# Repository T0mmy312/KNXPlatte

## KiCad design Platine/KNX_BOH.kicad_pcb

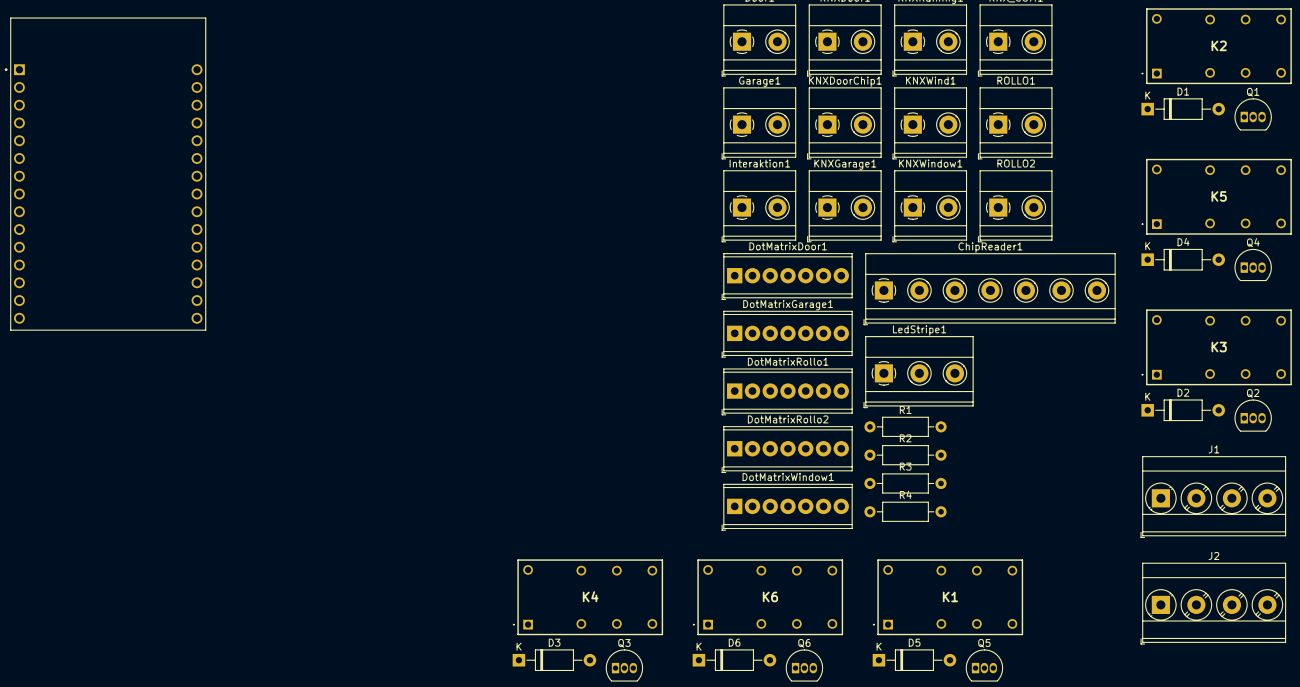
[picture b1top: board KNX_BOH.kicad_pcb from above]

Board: 2 copper layers, 44 parts (0 on the bottom side), 49 nets, no tracks yet.

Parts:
ChipReader1: Screw_Terminal_01x07; TerminalBlock_Phoenix_MKDS-1,5-7-5.08_1x07_P5.08mm_Horizont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
D1, D2, D3, D4, D5, D6: D; D_A-405_P10.16mm_Horizontal
Door1: Screw_Terminal_01x02; TerminalBlock_Phoenix_MKDS-1,5-2-5.08_1x02_P5.08mm_Horizont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
DotMatrixDoor1: Screw_Terminal_01x05; TerminalBlock_Phoenix_MPT-0,5-7-2.54_1x07_P2.54mm_Horizontal
DotMatrixGarage1: Screw_Terminal_01x05; TerminalBlock_Phoenix_MPT-0,5-7-2.54_1x07_P2.54mm_Horizontal
DotMatrixRollo1, DotMatrixRollo2: Screw_Terminal_01x05; TerminalBlock_Phoenix_MPT-0,5-7-2.54_1x07_P2.54mm_Horizontal
DotMatrixWindow1: Screw_Terminal_01x05; TerminalBlock_Phoenix_MPT-0,5-7-2.54_1x07_P2.54mm_Horizontal
ESP32_WROOM_32D_USB-C2: ESP32_WROOM_32D_USB-C
Garage1: Screw_Terminal_01x02; TerminalBlock_Phoenix_MKDS-1,5-2-5.08_1x02_P5.08mm_Horizont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
Interaktion1: Screw_Terminal_01x02; TerminalBlock_Phoenix_MKDS-1,5-2-5.08_1x02_P5.08mm_Horizont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
J1, J2: Conn_01x04_Pin; TerminalBlock_Phoenix_MKDS-3-4-5.08_1x04_P5.08mm_Horizontal
K1, K2, K3, K4, K5, K6: DSBT2-S-DC24V; DSBT2SDC24V
KNXDoor1: Screw_Terminal_01x02; TerminalBlock_Phoenix_MKDS-1,5-2-5.08_1x02_P5.08mm_Horizont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
KNXDoorChip1: Screw_Terminal_01x02; TerminalBlock_Phoenix_MKDS-1,5-2-5.08_1x02_P5.08mm_Horizont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
KNXGarage1: Screw_Terminal_01x02; TerminalBlock_Phoenix_MKDS-1,5-2-5.08_1x02_P5.08mm_Horizont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
KNXRaining1: Screw_Terminal_01x02; TerminalBlock_Phoenix_MKDS-1,5-2-5.08_1x02_P5.08mm_Horizont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
KNXWind1: Screw_Terminal_01x02; TerminalBlock_Phoenix_MKDS-1,5-2-5.08_1x02_P5.08mm_Horizont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
KNXWindow1: Screw_Terminal_01x02; TerminalBlock_Phoenix_MKDS-1,5-2-5.08_1x02_P5.08mm_Horizont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
KNX_COM1: Screw_Terminal_01x02; TerminalBlock_Phoenix_MKDS-1,5-2-5.08_1x02_P5.08mm_Horizont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
LedStripe1: Screw_Terminal_01x03; TerminalBlock_Phoenix_MKDS-1,5-3-5.08_1x03_P5.08mm_Horizont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
Q1, Q2, Q3, Q4, Q5, Q6: BC547; TO-92_Inline
R1, R2, R3, R4: 10k; R_Axial_DIN0207_L6.3mm_D2.5mm_P10.16mm_Horizontal
ROLLO1, ROLLO2: Screw_Terminal_01x02; TerminalBlock_Phoenix_MKDS-1,5-2-5.08_1x02_P5.08mm_Horizont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

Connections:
+3V3: DotMatrixDoor1.1, DotMatrixGarage1.1, DotMatrixRollo1.1, DotMatrixRollo2.1, DotMatrixWindow1.1, ESP32_WROOM_32D_USB-C2.1 (3V3), R1.1, R2.1, R3.1, R4.1
+5V: ChipReader1.1, ESP32_WROOM_32D_USB-C2.16 (VIN), LedStripe1.1, Q1.1 (C), Q2.1 (C), Q3.1 (C), Q4.1 (C), Q5.1 (C), Q6.1 (C)
/Relais1/Relais_COM: K1.4 (COM_1), K1.13 (COM_2), KNXRaining1.2
/Relais1/Relais_OUT: K1.8 (N.O._1), K1.9 (N.O._2), KNXRaining1.1
/Relais2/Relais_COM: K2.4 (COM_1), K2.13 (COM_2), KNXWind1.2
/Relais2/Relais_OUT: K2.8 (N.O._1), K2.9 (N.O._2), KNXWind1.1
/Relais3/Relais_COM: K3.4 (COM_1), K3.13 (COM_2), KNXDoor1.2
/Relais3/Relais_OUT: K3.8 (N.O._1), K3.9 (N.O._2), KNXDoor1.1
/Relais4/Relais_COM: K4.4 (COM_1), K4.13 (COM_2), KNXDoorChip1.2
/Relais4/Relais_OUT: K4.8 (N.O._1), K4.9 (N.O._2), KNXDoorChip1.1
/Relais5/Relais_COM: K5.4 (COM_1), K5.13 (COM_2), KNXGarage1.2
/Relais5/Relais_OUT: K5.8 (N.O._1), K5.9 (N.O._2), KNXGarage1.1
/Relais6/Relais_COM: K6.4 (COM_1), K6.13 (COM_2), KNXWindow1.2
/Relais6/Relais_OUT: K6.8 (N.O._1), K6.9 (N.O._2), KNXWindow1.1
CS_ChipReader: ChipReader1.7, ESP32_WROOM_32D_USB-C2.26 (D35)
CS_DotMatrixDoor: DotMatrixDoor1.4, ESP32_WROOM_32D_USB-C2.14 (D22)
CS_DotMatrixGarage: DotMatrixGarage1.4, ESP32_WROOM_32D_USB-C2.25 (D32)
CS_DotMatrixRollo1: DotMatrixRollo1.4, ESP32_WROOM_32D_USB-C2.24 (D33)
CS_DotMatrixRollo2: DotMatrixRollo2.4, ESP32_WROOM_32D_USB-C2.23 (D25)
CS_DotMatrixWindow: DotMatrixWindow1.4, ESP32_WROOM_32D_USB-C2.22 (D26)
GND: ChipReader1.3, D1.2 (A), D2.2 (A), D3.2 (A), D4.2 (A), D5.2 (A), D6.2 (A), DotMatrixDoor1.2, DotMatrixGarage1.2, DotMatrixRollo1.2, DotMatrixRollo2.2, DotMatrixWindow1.2, ESP32_WROOM_32D_USB-C2.2 (GND), ESP32_WROOM_32D_USB-C2.17 (GND), J1.4, J2.4, K1.16 (COIL-), K2.16 (COIL-), K3.16 (COIL-), K4.16 (COIL-), K5.16 (COIL-), K6.16 (COIL-), KNX_COM1.1, KNX_COM1.2, LedStripe1.3
KNX_Cooling: ESP32_WROOM_32D_USB-C2.28 (VN), Interaktion1.2
KNX_Garage_UP: ESP32_WROOM_32D_USB-C2.8 (D5), Garage1.1
KNX_Heating: ESP32_WROOM_32D_USB-C2.29 (VP), Interaktion1.1
KNX_ROLLO_1_DOWN: ESP32_WROOM_32D_USB-C2.19 (D12), ROLLO1.2
KNX_ROLLO_1_UP: ESP32_WROOM_32D_USB-C2.18 (D13), ROLLO1.1
KNX_ROLLO_2_DOWN: ESP32_WROOM_32D_USB-C2.21 (D27), ROLLO2.2
KNX_ROLLO_2_UP: ESP32_WROOM_32D_USB-C2.20 (D14), ROLLO2.1
KNX_Tür: Door1.1, ESP32_WROOM_32D_USB-C2.11 (D21)
MISO: ChipReader1.4, ESP32_WROOM_32D_USB-C2.10 (D19)
MOSI: ChipReader1.5, DotMatrixDoor1.3, DotMatrixGarage1.3, DotMatrixRollo1.3, DotMatrixRollo2.3, DotMatrixWindow1.3, ESP32_WROOM_32D_USB-C2.15 (D23)
unnamed: D1.1 (K), K2.1 (COIL+), Q1.3 (E)
unnamed: D2.1 (K), K3.1 (COIL+), Q2.3 (E)
unnamed: D3.1 (K), K4.1 (COIL+), Q3.3 (E)
unnamed: D4.1 (K), K5.1 (COIL+), Q4.3 (E)
unnamed: D5.1 (K), K1.1 (COIL+), Q5.3 (E)
unnamed: D6.1 (K), K6.1 (COIL+), Q6.3 (E)
unnamed: K1.6 (N.C._1), K1.11 (N.C._2)
unnamed: K2.6 (N.C._1), K2.11 (N.C._2)
unnamed: K3.6 (N.C._1), K3.11 (N.C._2)
unnamed: K4.6 (N.C._1), K4.11 (N.C._2)
unnamed: K5.6 (N.C._1), K5.11 (N.C._2)
unnamed: K6.6 (N.C._1), K6.11 (N.C._2)
RST_ChipReader: ChipReader1.2, ESP32_WROOM_32D_USB-C2.27 (D34)
Rain_Automatic: ESP32_WROOM_32D_USB-C2.3 (D15), J1.1, R1.2
Rain_Manual: ESP32_WROOM_32D_USB-C2.5 (D4), J1.3, R2.2
SCK: ChipReader1.6, DotMatrixDoor1.5, DotMatrixGarage1.5, DotMatrixRollo1.5, DotMatrixRollo2.5, DotMatrixWindow1.5, ESP32_WROOM_32D_USB-C2.9 (D18)
Wind_Automatic: ESP32_WROOM_32D_USB-C2.6 (D16), J2.1, R3.2
Wind_Manual: ESP32_WROOM_32D_USB-C2.7 (D17), J2.3, R4.2

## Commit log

2025-01-14 implemented Door class
2025-01-14 added led strip segment class and untested Weather class
2025-01-21 add running files
2025-01-21 add platine files from 14.1.25
2025-01-21 cleaned up file structure
2025-01-21 finished Weather class and implemented GarageDoor and a 3d Window
2025-02-04 esp zu knx io pin list added
2025-02-04 made that lukas likes it
2025-02-04 added pin list
2025-02-04 added Heater class
2025-02-04 updated window for less inputs
2025-02-04 Platine fast fertig
2025-02-11 finished schematic
2025-02-11 added LocalDotmatrix so everything can go on the same cs pin
2025-02-11 updated all Dotmatrix classes to use LocalDotmatrix and adjusted the config file
2025-02-11 made a inputConfig header file and changed the code to work with bool functions instead of fixed pins for more configureable inputs
